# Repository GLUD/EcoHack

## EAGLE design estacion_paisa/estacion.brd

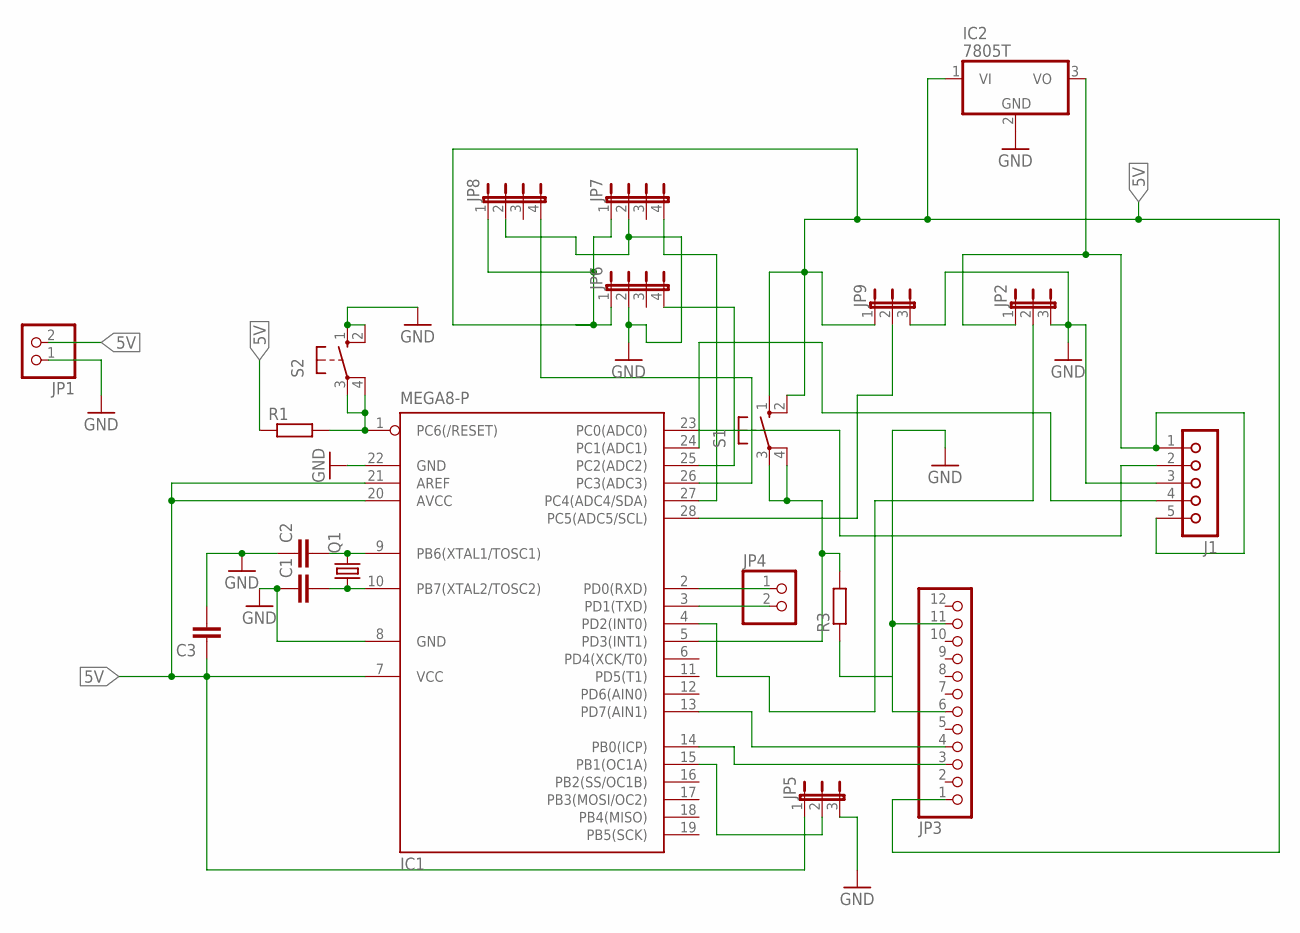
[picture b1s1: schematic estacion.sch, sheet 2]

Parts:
C1, C2, C3: C2,5-3; C2.5-3
IC1: MEGA8-P; DIL28-3
IC2: 7805T; TO220H
J1: JU05
JP1, JP4: PINHD-1X2; 1X02
JP2, JP5, JP9: JP2W
JP3: PINHD-1X12; 1X12
JP6, JP7, JP8: JP4E; JP4
Q1: CRYSTALTC26V; TC26V
R1, R3: R-EU_0204/5; 0204/5
S1, S2: 10-XX; B3F-10XX

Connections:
5V: C3.1, IC1.7 (VCC), IC1.20 (AVCC), IC1.21 (AREF), IC2.1 (VI), JP1.2, JP3.1, JP5.1, JP6.1, JP7.1, JP8.1, JP9.1, R1.1, S1.1 (S), S1.2 (S1)
GND: C1.1, C2.1, C3.2, IC1.8 (GND), IC1.22 (GND), IC2.2 (GND), J1.3, JP1.1, JP2.3, JP3.6, JP3.11, JP5.3, JP6.2, JP7.2, JP8.2, JP9.3, R3.1, S2.1 (S), S2.2 (S1)
unnamed: IC1.14 (PB0(ICP)), JP3.3
unnamed: IC1.13 (PD7(AIN1)), JP3.4
unnamed: IC1.5 (PD3(INT1)), R3.2, S1.3, S1.4 (P1)
unnamed: IC1.3 (PD1(TXD)), JP4.2
unnamed: IC1.4 (PD2(INT0)), JP2.2
unnamed: IC1.2 (PD0(RXD)), JP4.1
unnamed: IC1.15 (PB1(OC1A)), JP5.2
unnamed: IC2.3 (VO), J1.1, J1.5, JP2.1
unnamed: IC1.25 (PC2(ADC2)), JP6.4
unnamed: IC1.28 (PC5(ADC5/SCL)), JP9.2
unnamed: IC1.27 (PC4(ADC4/SDA)), JP7.4
unnamed: C2.2, IC1.9 (PB6(XTAL1/TOSC1)), Q1.2
unnamed: C1.2, IC1.10 (PB7(XTAL2/TOSC2)), Q1.1
unnamed: IC1.1 (PC6(/RESET)), R1.2, S2.3, S2.4 (P1)
unnamed: IC1.23 (PC0(ADC0)), J1.4
unnamed: IC1.26 (PC3(ADC3)), JP8.4
unnamed: IC1.24 (PC1(ADC1)), J1.2

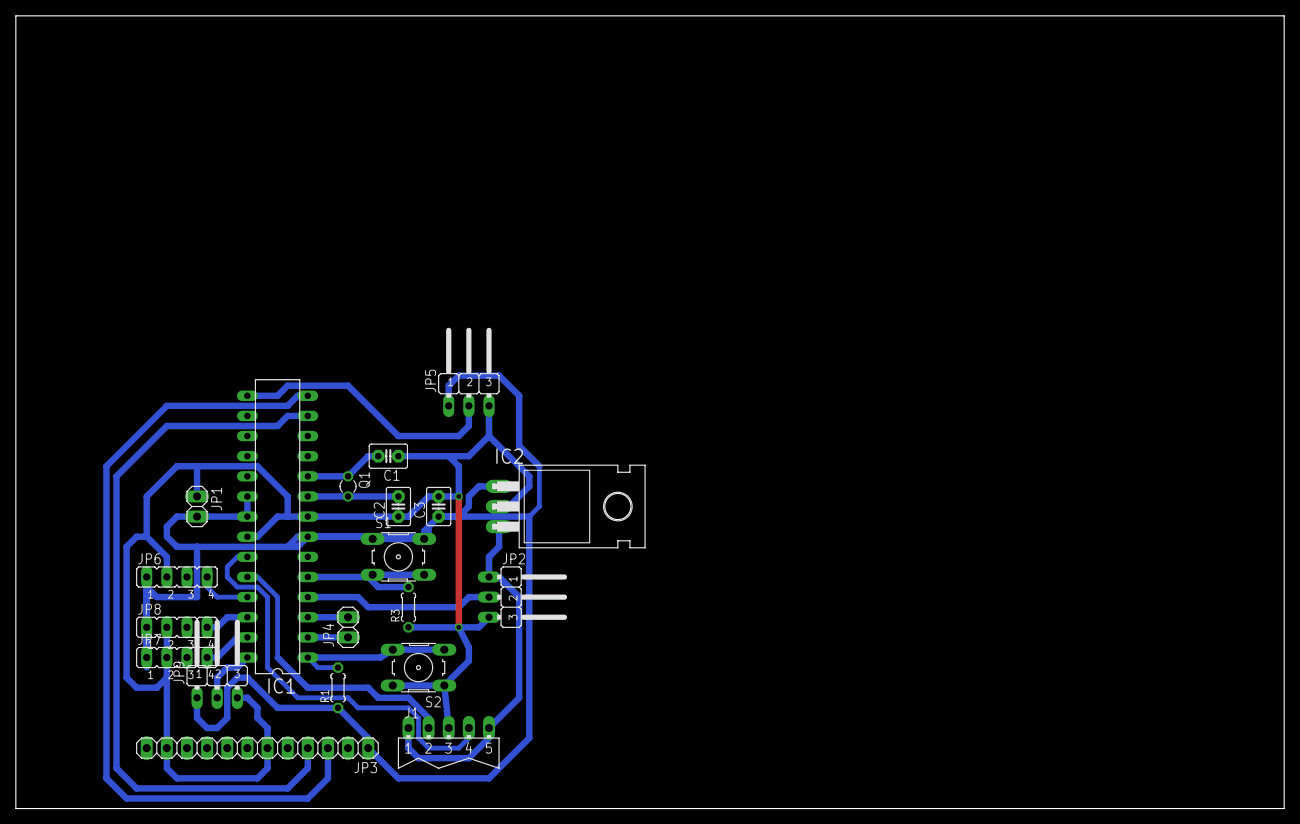
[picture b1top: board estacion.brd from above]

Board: 2 copper layers, 160.0 x 100.0 mm, 20 parts (0 on the bottom side), 19 nets.

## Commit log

2015-12-06 Arranque y adquisición de datos
2015-12-06 cambio de nombre para reducir longitud de peticiones
2015-12-06 se sube codigo de lectura de datos ambientales
2015-12-11 Se sube mapa georeferencia y graficas de datos capturados
2015-12-11 Se actualiza el codigo final de envio de datos
2015-12-11 Diseños electrónicos
2015-12-11 arquitectura en pdf
2015-12-13 Agregado registro de emplazamiento y usuarios
2015-12-23 El hijueputa commit que no hicieron!!!!
2015-12-23 Correccion formularios bonitos
2015-12-23 Se crea un formulario con validacion
2015-12-23 se crea slider de imagenes
2016-01-13 se agrego validacion de formulario y se corrigieron errores
2016-01-13 se agrego campo de fotoy validacion
2016-01-13 se agrego slider responsive, menu superior
2016-01-13 sincronizacion del servidor de pruebas
2016-01-14 se agrego validacion y campo foto con codificacion base 64
2016-01-14 campo foto con codificacion base 64
